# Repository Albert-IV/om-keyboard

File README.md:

# Om Keyboard

Right now I'm iterating on a 34 key split that uses MX spacing horiontally and choc spacing vertically.  Uses the splay from the Absolem keyboard and the lowered thumb keys of the Draculad.  

# Photos
## Rev 1 Photos

## Rev 0 Photos

# Notes

## Rev 1
Rev 0 was a pretty good success, though there are other tweaks that need to be made.  

Pinkies were not staggered enough I've found after trying out the Osprette keyboard.  The Osprette features a home pinky location that's equal to the bottom key of the ring finger and feels really comfortable / right.  Attempted to do the same for the pointer finger keys, however with such advanced stagger could not comfortably reach the bottom inner column keys.  30-key keyboards maybe have a point?

Additionally wanted to change the location of the ring finger as well.  Right now my ring finger naturally wants to rest on the outer ridge of the ring finger home key.  To compensate, I moved the key about a third of a U over, increasing the spave to hopefully feel correct. Looking at the spacing, this begs for splay, but will save this for the next iteration for now.  

Lastly I wanted to change the thumbs a _touch_ though not a ton as they felt pretty good.  I do feel like they may be a little low, but possibly not.  With MBK profile keycaps the thumbs weren't ultra comfortable, but once moved to CS felt great.  Actuating the key leverages the top joint of your thumb rather than the thumb tip, which for some may be optimal.  I chew my fingers a lot, so avoiding having to actuate with the side of my thumb nail where there may be hangnails is a feature, not a bug.

I still did move the thumbs up a touch.  Just a smidge.  It's hard to tell, as I had a key incorrectly placed inside my Ergogen config that made thumb positioning unreliable and reliant on other keys locations.  Future iterations will have a corrected config which will be rock solid, but for now I eyeballed positioning and hope it works out.  I do want to play with thumb rotation, but I'm unsure how to measure that.  When using arm rests my thumb arc looks one way, and while resting on the table the thumbs arc in a slightly different line.  May want to use some combination of the two?  Not sure.

Next iteration will leverage cardboard cutouts, so that I can put in switches and test drive on next layout iteration to fully dial in positioning.  Overall rev0 did feel comfortable, but not 100% perfect. I may play with an Osprette-like pinky cluster in the future, bumping the key count to 36 keys temporarily.

## Rev 0
Initial prototype using 34 keys, choc spacing vertically and MX spacing horizontally with a deep thumb a la Draculad and a touch of splay stolen from the Absolum.

PCB's were ordered from JLCPCB and built roughly Feb 23-24th 2022.  Used as a daily driver for about a month before making iterations for Rev 1

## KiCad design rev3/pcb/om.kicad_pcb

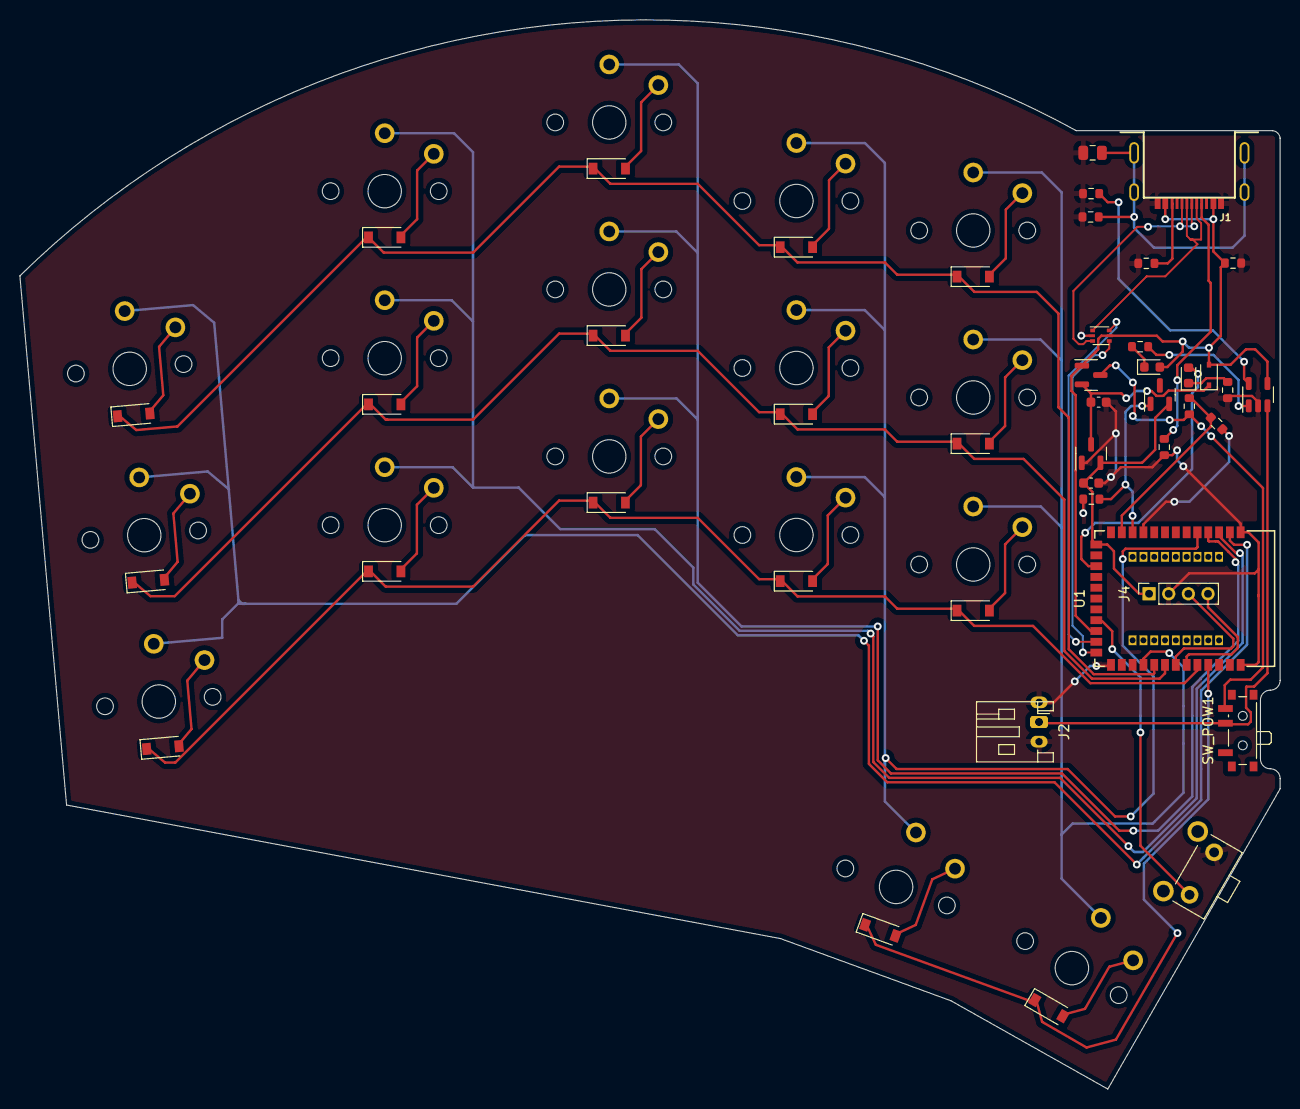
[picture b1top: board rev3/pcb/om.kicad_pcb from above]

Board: 2 copper layers, 128.3 x 108.8 mm, 62 parts (1 on the bottom side), 50 nets.

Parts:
C1, C2: 1uF; C_0603_1608Metric
C3: 4.7n; C_0805_2012Metric
D1: D_Schottky; D_SOD-323
D2: Blue LED; LED_0603_1608Metric
D3: Red LED; LED_0603_1608Metric
DIODE1, DIODE2, DIODE3, DIODE4, DIODE5, DIODE6, DIODE7, DIODE8, DIODE9, DIODE10, DIODE11, DIODE12, DIODE13, DIODE14, DIODE15, DIODE16, DIODE17: 1N914WT; D_SOD-123
ESD1: USBLC6-2P6; SOT-666
J1: USB_C_Receptacle; USB-C-12-Pin-MidMount
J2, J3: JST-BATT; JST_PH_S2B-PH-K_1x02_P2.00mm_Horizontal
J4: SWD; PinSocket_1x04_P2.00mm_Vertical
Q1, Q2: AO3407; SOT-23
R1: 100K; R_0603_1608Metric
R2: 1M; R_0603_1608Metric
R3, R7: 2M; R_0603_1608Metric
R4, R5: 5.1K; R_0603_1608Metric
R6: 806/820k; R_0603_1608Metric
R8, R9: 1K; R_0603_1608Metric
R10: 10K; R_0603_1608Metric
R_TACT1: SW_Push; SKHLLCA010
SW1, SW2, SW3, SW4, SW5, SW6, SW7, SW8, SW9, SW10, SW11, SW12, SW13, SW14, SW15, SW16, SW17: Choc; pg1350
SW_POW1: SW_SPDT; SW_SPDT_PCM12
U1: nRF52840_holyiot_18010; holyiot-18010
U2: XC6206P LDO; SOT-23
U3: LTC4054ES5-4.2; TSOT-23-5

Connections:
+3V3: C2.1, J4.1, Q2.2 (S), U1.55 (VDD), U2.2 (VO)
+BATT: J2.1, J3.1 (2), SW_POW1.2 (B), U3.3 (BAT)
/BAT+_SWITCHED: Q1.3 (D), R6.1, SW_POW1.3 (C)
/Net-(U3-PROG): R10.2, U3.5 (PROG)
/V-IN: C1.1, D1.1 (K), Q1.2 (S), U2.3 (VI)
BLUE_LED: D2.2 (A), U1.53 (P1.09)
Col1: SW1.1, SW2.1, SW3.1, U1.2 ([L]_P1.11)
Col2: SW4.1, SW5.1, SW6.1, U1.3 ([L]_P1.10)
Col3: SW7.1, SW8.1, SW9.1, U1.4 ([L]_P1.13)
Col4: SW10.1, SW11.1, SW12.1, SW16.1, U1.5 ([L]_P1.15)
Col5: SW13.1, SW14.1, SW15.1, SW17.1, U1.41 ([L]_P1.03)
D+: ESD1.4 (I/O2), U1.45 (D+)
D-: ESD1.6 (I/O1), U1.46 (D-)
Earth: C3.2, J1.S1 (SHIELD), R2.2
GND: C1.2, C2.2, C3.1, ESD1.2 (GND), J1.A1 (GND), J2.2, J3.2 (1), J4.2, R1.2, R2.1, R3.2, R4.2, R5.2, R8.2, R10.1, R_TACT1.2, U1.1 (GND), U1.32 (GND), U1.44 (GND), U2.1 (GND), U3.2 (GND)
unnamed: D2.1 (K), R8.1
unnamed: D3.1 (K), R9.1
unnamed: DIODE1.2 (A), SW1.2
unnamed: DIODE3.2 (A), SW3.2
unnamed: DIODE4.2 (A), SW4.2
unnamed: DIODE5.2 (A), SW5.2
unnamed: DIODE6.2 (A), SW6.2
unnamed: DIODE7.2 (A), SW7.2
unnamed: DIODE8.2 (A), SW8.2
unnamed: DIODE9.2 (A), SW9.2
unnamed: DIODE10.2 (A), SW10.2
unnamed: DIODE12.2 (A), SW12.2
unnamed: J1.A5 (CC1), R5.1
unnamed: J1.B5 (CC2), R4.1
unnamed: R9.2, U3.1 (~CHRG)
unnamed: DIODE2.2 (A), SW2.2
unnamed: DIODE11.2 (A), SW11.2
unnamed: DIODE13.2 (A), SW13.2
unnamed: DIODE14.2 (A), SW14.2
unnamed: DIODE15.2 (A), SW15.2
unnamed: DIODE16.2 (A), SW16.2
unnamed: DIODE17.2 (A), SW17.2
RESET: R_TACT1.1, U1.48 (Reset/P0.18)
Row1: DIODE1.1 (K), DIODE4.1 (K), DIODE7.1 (K), DIODE10.1 (K), DIODE13.1 (K), U1.40 ([L]_P1.01)
Row2: DIODE2.1 (K), DIODE5.1 (K), DIODE8.1 (K), DIODE11.1 (K), DIODE14.1 (K), U1.39 ([L]_P1.02)
Row3: DIODE3.1 (K), DIODE6.1 (K), DIODE9.1 (K), DIODE12.1 (K), DIODE15.1 (K), U1.36 ([L]_P1.04)
Row4: DIODE16.1 (K), DIODE17.1 (K), U1.35 ([L]_P1.06)
SWDCLK: J4.3, U1.38 (SWC)
SWDIO: J4.4, U1.37 (SWD)
USBD+: ESD1.3 (I/O2), J1.A6 (D+), J1.B6 (D+)
USBD-: ESD1.1 (I/O1), J1.A7 (D-), J1.B7 (D-)
VBUS: D1.2 (A), D3.2 (A), ESD1.5 (VBUS), J1.A4 (VBUS), Q1.1 (G), R1.1, U1.47 (VBUS), U3.4 (VCC)
VCC_CONTROL: Q2.1 (G), R3.1, U1.11 ([L]_A7_P0.31)
VSENSE: R6.2, R7.1, U1.12 (A2_P0.04)
VSENSE_ENABLE: R7.2, U1.10 ([L]_A6_P0.30)

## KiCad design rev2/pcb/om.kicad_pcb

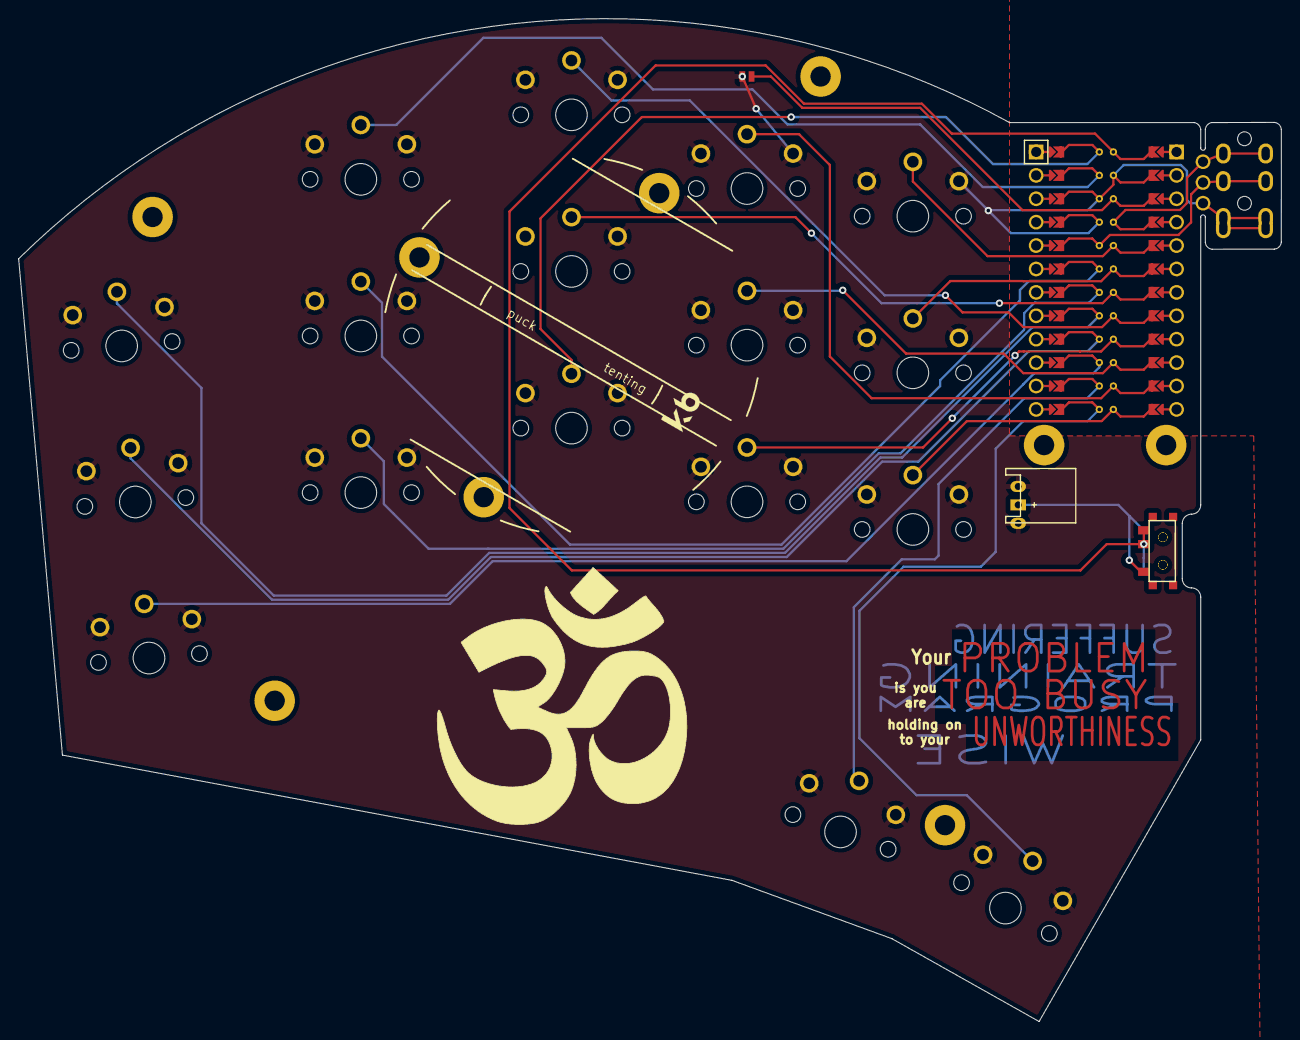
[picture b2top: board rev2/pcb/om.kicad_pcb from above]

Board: 2 copper layers, 137.0 x 108.8 mm, 23 parts (1 on the bottom side), 21 nets.

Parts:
J1: Jumper
JST1: JST_PH_S2B-PH-K_02x2.00mm_Angled
MCU1: ProMicro
S1, S2, S3, S4, S5, S6, S7, S8, S9, S10, S11, S12, S13, S14, S15, S16, S17: PG1350
T1, T1#2: SPDT_C128955
_1: Tenting Puck

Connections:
GND: J1.1, JST1.1, JST1.2, MCU1.2, MCU1.21, MCU1.22, S1.1, S2.1, S3.1, S4.1, S5.1, S6.1, S7.1, S8.1, S9.1, S10.1, S11.1, S12.1, S13.1, S14.1, S15.1, S16.1, S17.1
P0: MCU1.23, S6.2
P1: MCU1.24, S7.2
P3: MCU1.19, S5.2
P4: MCU1.18, S4.2
P5: MCU1.17, S3.2
P6: MCU1.16, S2.2
P7: MCU1.15, S1.2
P8: MCU1.14, S16.2
P9: MCU1.13, S17.2
P10: MCU1.12, S13.2
P14: MCU1.10, S11.2
P15: MCU1.9, S10.2
P16: MCU1.11, S12.2
P18: MCU1.8, S9.2
P19: MCU1.7, S8.2
P20: MCU1.6, S14.2
P21: MCU1.5, S15.2
POSITIVE: JST1.1, T1.1, T1#2.1
RAW: MCU1.1, T1.2, T1.3, T1#2.2, T1#2.3
RST: J1.2, MCU1.3

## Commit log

2022-01-09 Set up initial process for project. Added 34 key layout for later work.
2022-02-07 Set up working PCB for Github Actions
2022-02-13 Sent off to allpcb
2022-03-15 Rename cockamamie -> Om
2022-03-15 Added Rev 0 images
2022-03-17 Added rev1 of the board
2022-03-17 Updated Om silkscreens to look more dynamic
2022-03-17 swapping computers
2022-03-17 Fixed unreliable thumb rotations for future rev2. Updated readme with progress and thoughts on differences between rev0 and rev1 and why they were made
2022-03-17 Added gerbers
2022-04-16 Added rev 1 photos
2022-04-16 Added photos to README
2022-04-16 Changed up sections to feature photos first.
2022-04-18 Added reversible JST footprint. Added JST / reset jumper to board.
2022-06-19 With the new thumb anchor, closely matched positioning from rev1 PCB.
2022-06-19 Add some rotation to the thumb cluster so that the inner thumb key sits lower and "straighter" than previously
2022-06-25 Add rev 2 version of board, components are finalized, just need to polish
2022-06-26 Finished rev2 and added a choc mini variation
2022-07-01 Fix rev2 cutouts for on / off, add througholes for MCU cover, choc mini now has reversible mini footprints
2022-07-01 Created gerbers for rev 2 PCB
2022-07-02 Create the SVGs and DXF for creating the case
2022-07-03 Added a couple of cases... may or may not. Waiting on PCBs to arrive to test
2022-07-03 Move footprints folder to src
2022-07-03 Updated board outline, moved case files
2022-07-03 Added SVG / DXF of top case components for Fusion 360
2022-11-13 Started on onboard MCU version
2022-11-13 Fix the USB port connections, time to start routing
2022-11-19 Fix up the schematic -> footprint library usage. Pins were on the wrong pads.
2022-11-20 Routing might be done?
2022-12-12 Mostly in place, time to refactor
